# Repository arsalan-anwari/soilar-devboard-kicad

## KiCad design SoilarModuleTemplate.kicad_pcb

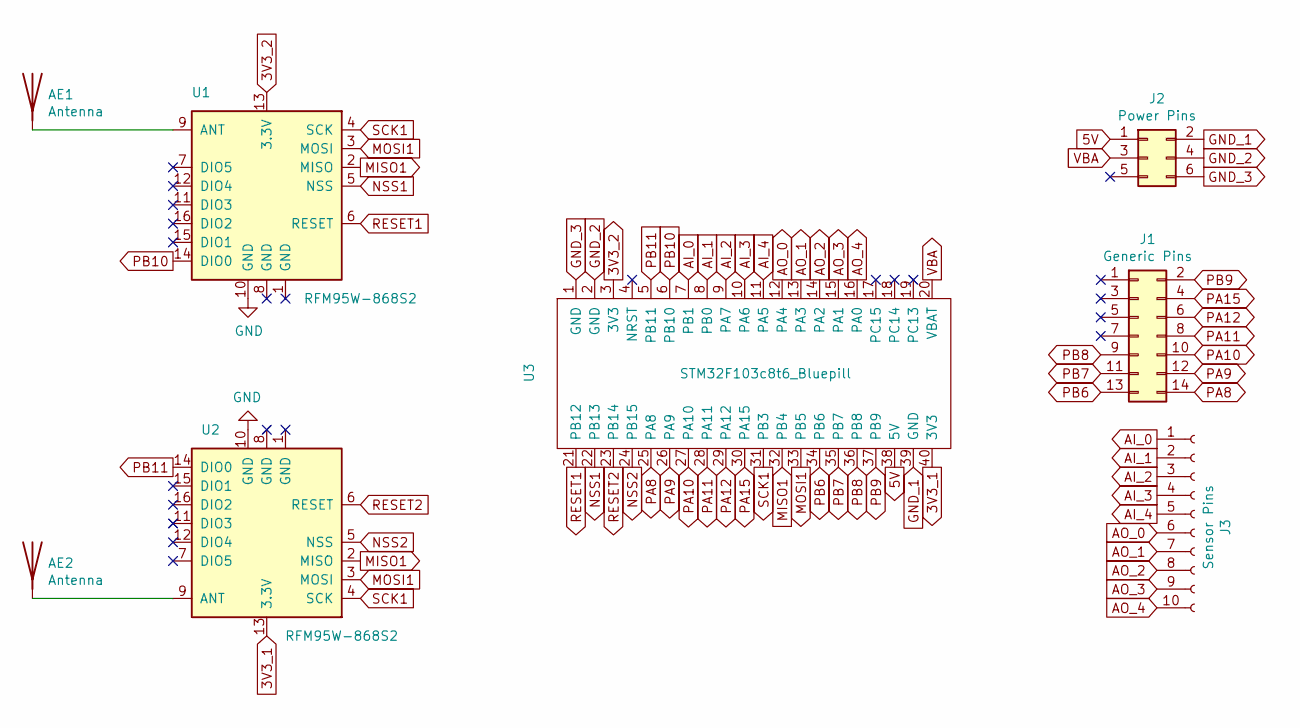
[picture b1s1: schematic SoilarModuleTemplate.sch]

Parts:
AE1, AE2: Antenna; Texas_SWRA416_868MHz_915MHz
J1: Generic Pins; PinHeader_2x07_P2.54mm_Vertical
J2: Power Pins; PinHeader_2x03_P2.54mm_Vertical
J3: Sensor Pins; PinHeader_1x10_P2.54mm_Horizontal
U1, U2: RFM95W-868S2; HOPERF_RFM9XW_THT
U3: STM32F103c8t6_Bluepill; STM32_103C8T6_Bluepill

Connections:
3V3_1: U2.13 (3.3V), U3.40 (3V3)
3V3_2: U1.13 (3.3V), U3.3 (3V3)
5V: J2.1, U3.38 (5V)
AI_0: J3.1, U3.7 (PB1)
AI_1: J3.2, U3.8 (PB0)
AI_2: J3.3, U3.9 (PA7)
AI_3: J3.4, U3.10 (PA6)
AI_4: J3.5, U3.11 (PA5)
AO_0: J3.6, U3.12 (PA4)
AO_1: J3.7, U3.13 (PA3)
AO_2: J3.8, U3.14 (PA2)
AO_3: J3.9, U3.15 (PA1)
AO_4: J3.10, U3.16 (PA0)
GND: U1.10 (GND), U2.10 (GND)
GND_1: J2.2, U3.39 (GND)
GND_2: J2.4, U3.2 (GND)
GND_3: J2.6, U3.1 (GND)
MISO1: U1.2 (MISO), U2.2 (MISO), U3.32 (PB4)
MOSI1: U1.3 (MOSI), U2.3 (MOSI), U3.33 (PB5)
NSS1: U1.5 (NSS), U3.22 (PB13)
NSS2: U2.5 (NSS), U3.24 (PB15)
unnamed: AE1.1, U1.9 (ANT)
unnamed: AE2.1, U2.9 (ANT)
PA8: J1.14, U3.25 (PA8)
PA9: J1.12, U3.26 (PA9)
PA10: J1.10, U3.27 (PA10)
PA11: J1.8, U3.28 (PA11)
PA12: J1.6, U3.29 (PA12)
PA15: J1.4, U3.30 (PA15)
PB6: J1.13, U3.34 (PB6)
PB7: J1.11, U3.35 (PB7)
PB8: J1.9, U3.36 (PB8)
PB9: J1.2, U3.37 (PB9)
PB10: U1.14 (DIO0), U3.6 (PB10)
PB11: U2.14 (DIO0), U3.5 (PB11)
RESET1: U1.6 (RESET), U3.21 (PB12)
RESET2: U2.6 (RESET), U3.23 (PB14)
SCK1: U1.4 (SCK), U2.4 (SCK), U3.31 (PB3)
VBA: J2.3, U3.20 (VBAT)

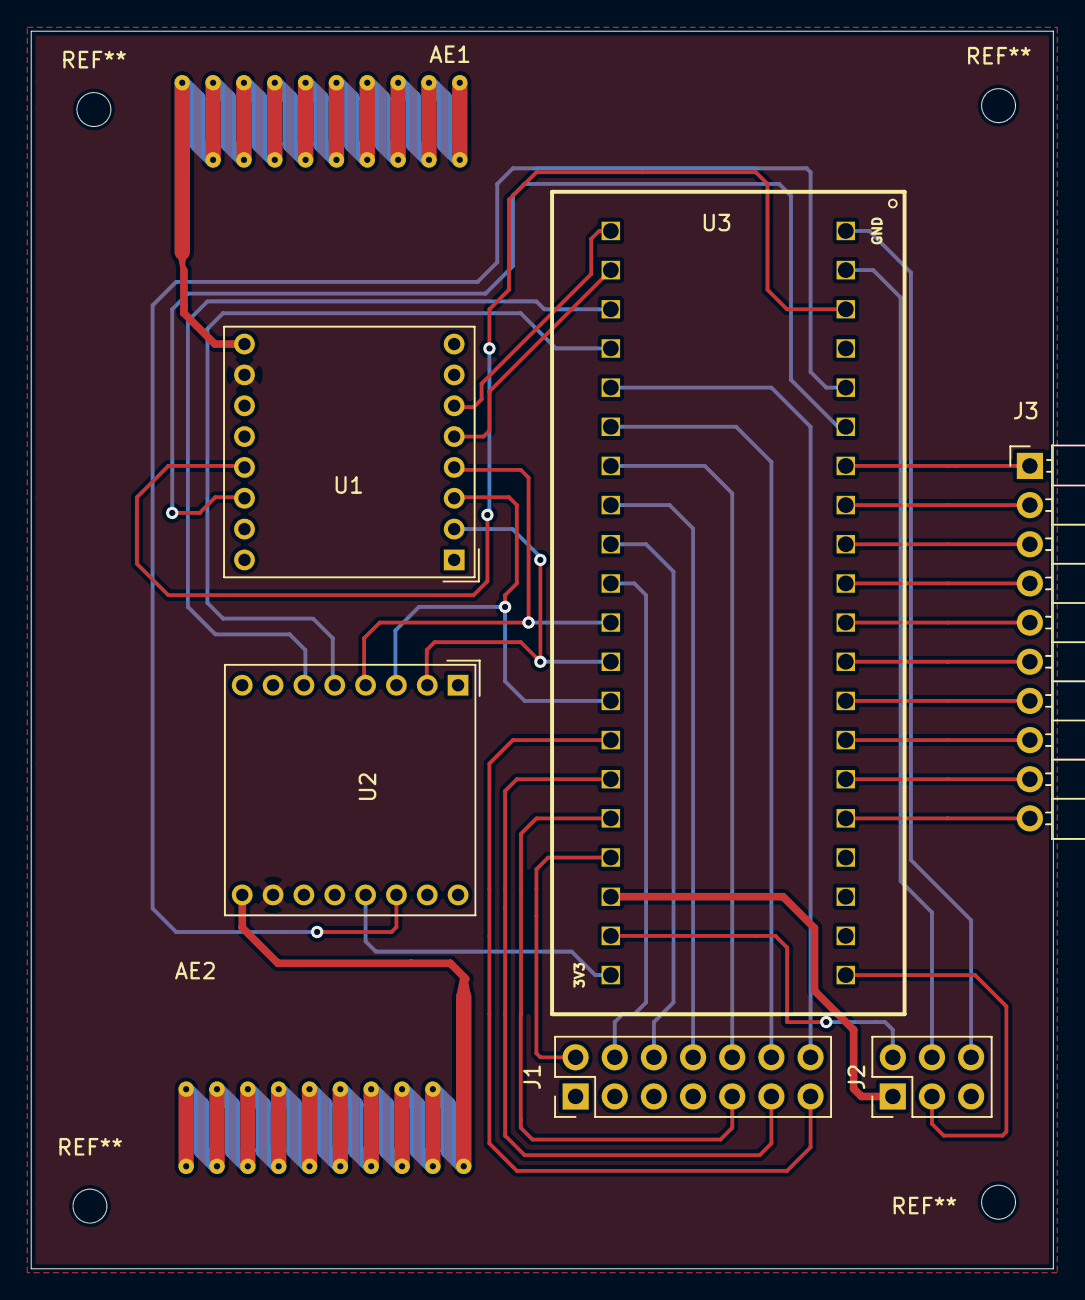
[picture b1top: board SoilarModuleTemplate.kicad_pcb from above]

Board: 2 copper layers, 66.3 x 80.3 mm, 8 parts (0 on the bottom side), 39 nets.

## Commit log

2023-01-10 README.md created online with Bitbucket
2023-01-10 Migrated files from soilarv1-kicad repo on github
